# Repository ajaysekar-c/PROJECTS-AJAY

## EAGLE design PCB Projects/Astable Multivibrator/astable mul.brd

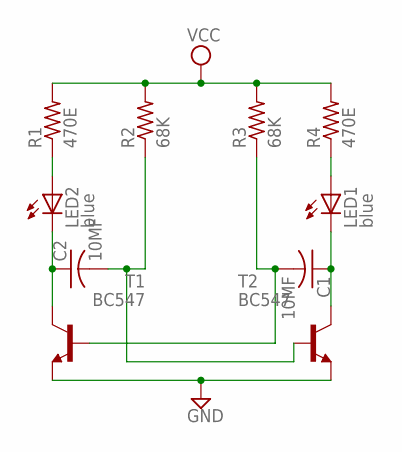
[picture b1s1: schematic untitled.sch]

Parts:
C1, C2: 10MF; C050-024X044
LED1, LED2: blue; LED5MM
R1, R4: 470E; 0207/10
R2, R3: 68K; 0207/10
T1, T2: BC547; TO92

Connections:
GND: T1.1 (E), T2.1 (E)
unnamed: LED2.A, R1.1
unnamed: C2.1, LED2.K (C), T1.3 (C)
unnamed: C1.1, LED1.K (C), T2.3 (C)
unnamed: LED1.A, R4.1
unnamed: C2.2, R2.1, T2.2 (B)
unnamed: C1.2, R3.1, T1.2 (B)
VCC: R1.2, R2.2, R3.2, R4.2

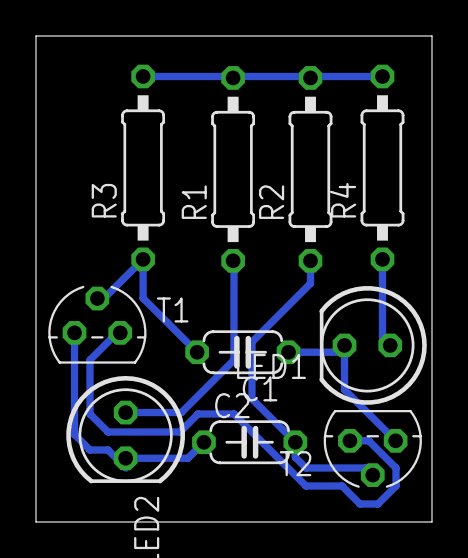
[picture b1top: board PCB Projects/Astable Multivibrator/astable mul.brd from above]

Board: 2 copper layers, 22.0 x 27.0 mm, 10 parts (0 on the bottom side), 8 nets.

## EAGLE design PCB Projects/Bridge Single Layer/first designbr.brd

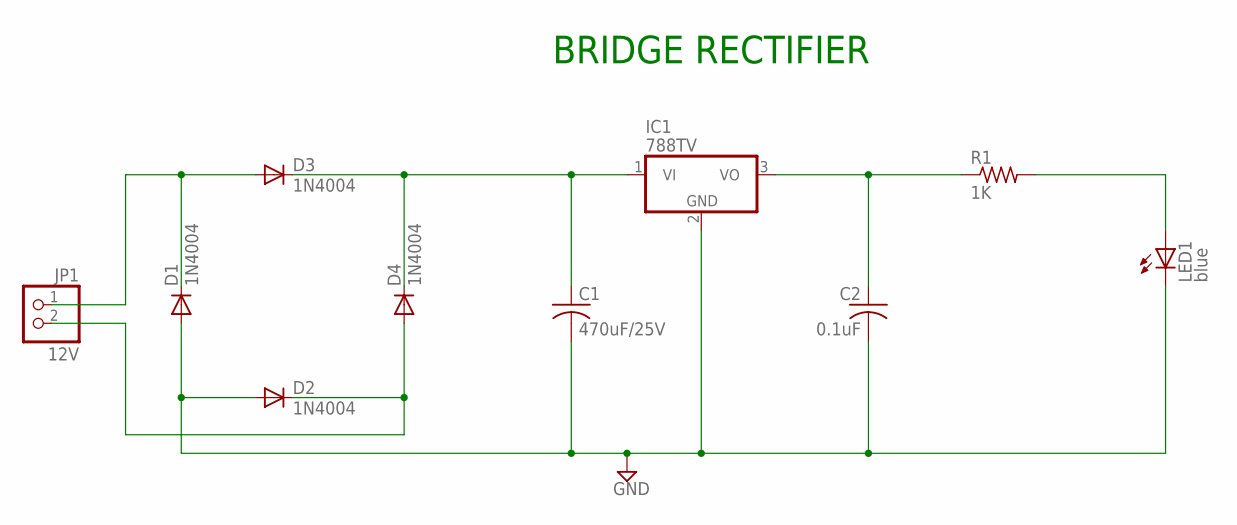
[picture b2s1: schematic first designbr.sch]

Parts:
C1: 470uF/25V; C050-025X075
C2: 0.1uF; C025-024X044
D1, D2, D3, D4: 1N4004; DO41-10
IC1: 788TV; TO220V
JP1: 12V; 1X02
LED1: blue; LED5MM
R1: 1K; 0207/10

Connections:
GND: C1.2, C2.2, D1.A, D2.A, IC1.2 (GND), LED1.K (C)
unnamed: D1.C, D3.A, JP1.1
unnamed: C1.1, D3.C, D4.C, IC1.1 (VI)
unnamed: D2.C, D4.A, JP1.2
unnamed: C2.1, IC1.3 (VO), R1.1
unnamed: LED1.A, R1.2

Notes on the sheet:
BRIDGE RECTIFIER

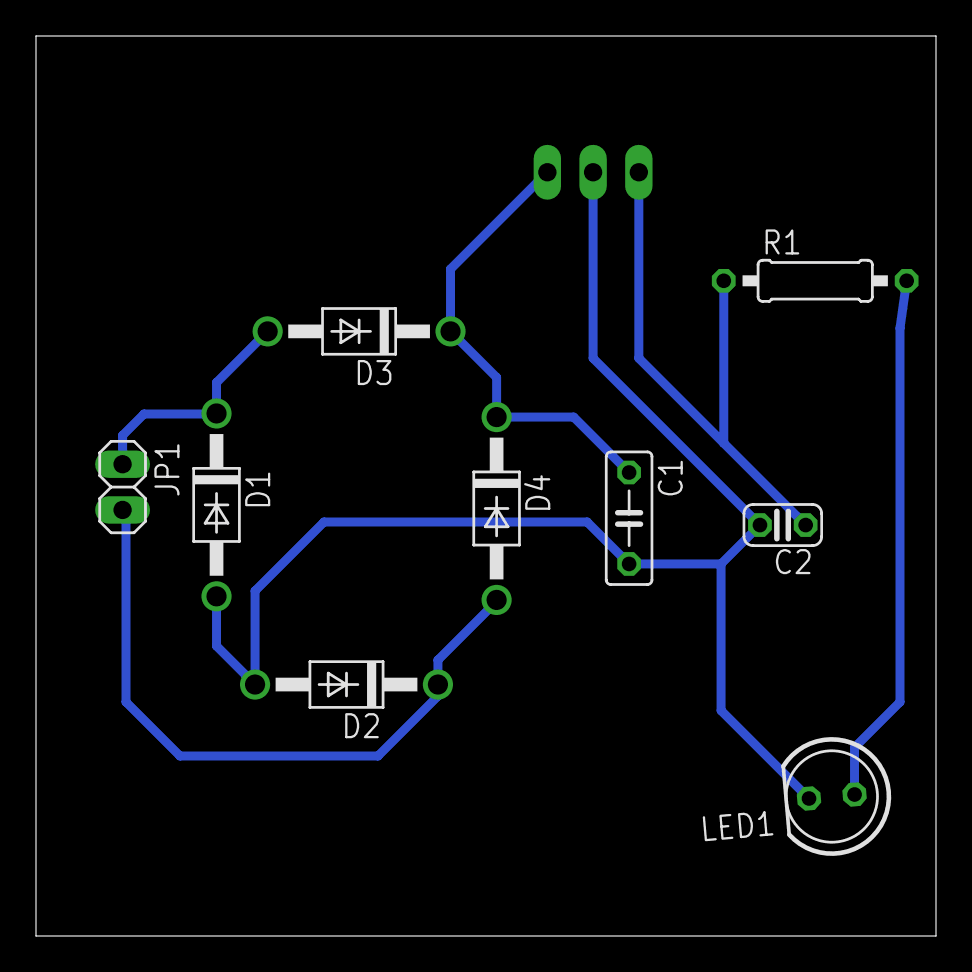
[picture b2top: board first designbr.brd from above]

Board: 2 copper layers, 50.0 x 50.0 mm, 10 parts (1 on the bottom side), 6 nets.

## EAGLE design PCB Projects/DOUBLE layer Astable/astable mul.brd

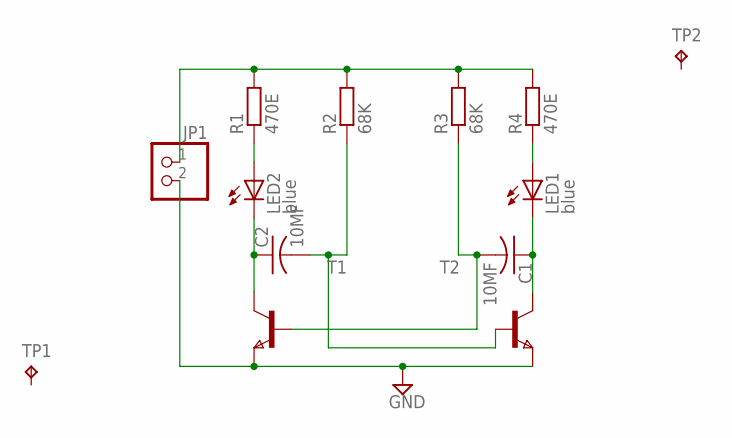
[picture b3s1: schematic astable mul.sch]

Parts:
C1, C2: 10MF; C050-025X075
JP1: PINHD-1X2; 1X02
LED1, LED2: blue; LED_1206
R1, R4: 470E; R0805
R2, R3: 68K; R0805
T1, T2: NPNSOT23; SOT-23
TP1, TP2: TPB1,27; B1,27

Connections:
GND: JP1.2, T1.2 (E), T2.2 (E)
unnamed: JP1.1, R1.2, R2.2, R3.2, R4.2
unnamed: LED2.A, R1.1
unnamed: C2.1, LED2.C, T1.1 (C)
unnamed: LED1.A, R4.1
unnamed: C1.1, LED1.C, T2.1 (C)
unnamed: C2.2, R2.1, T2.3 (B)
unnamed: C1.2, R3.1, T1.3 (B)

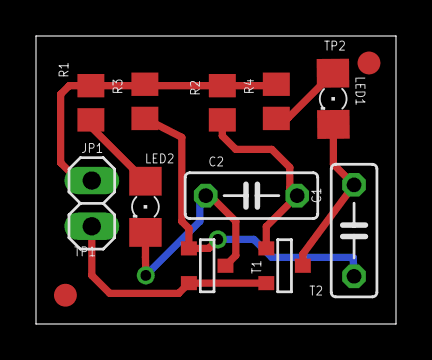
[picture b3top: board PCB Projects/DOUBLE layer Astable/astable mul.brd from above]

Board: 2 copper layers, 20.0 x 16.0 mm, 13 parts (0 on the bottom side), 8 nets.

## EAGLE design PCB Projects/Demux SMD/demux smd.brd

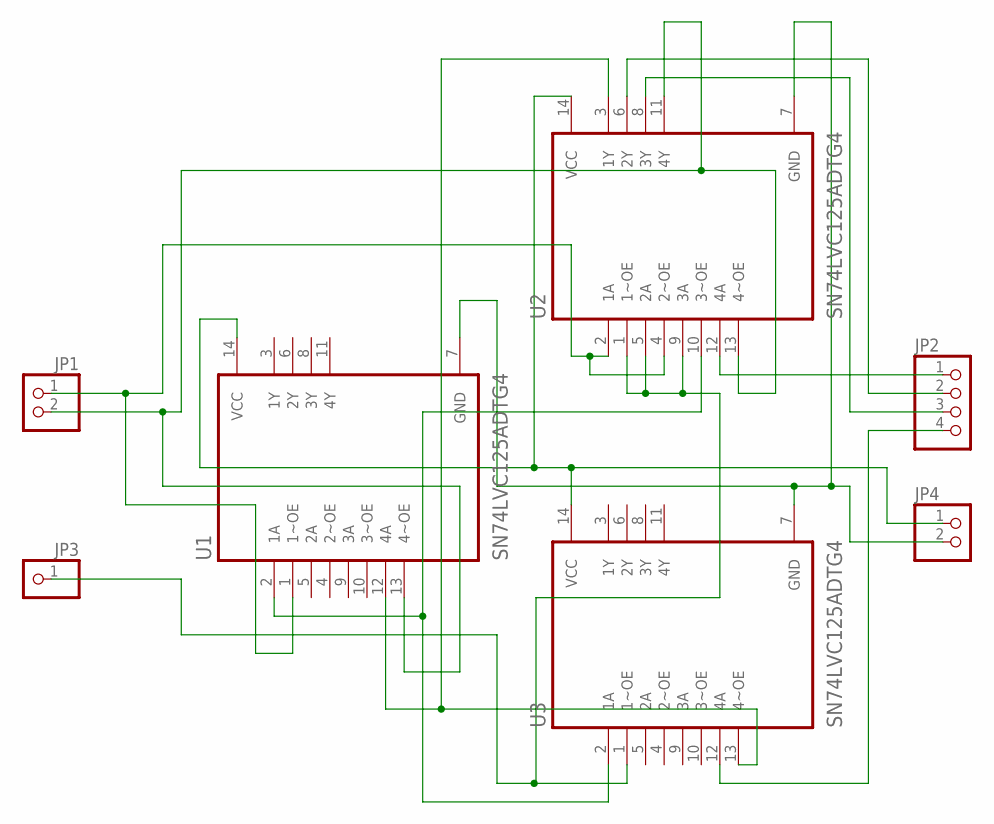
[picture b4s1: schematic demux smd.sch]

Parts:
JP1, JP4: PINHD-1X2; 1X02
JP2: PINHD-1X4; 1X04
JP3: PINHD-1X1; 1X01
U1, U2, U3: SN74LVC125ADTG4; SOIC127P600X175-14N

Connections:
unnamed: JP3.1, U2.1 (1~OE), U2.5 (2A), U2.9 (3A), U3.1 (1~OE)
unnamed: JP4.2, U1.7 (GND), U2.7 (GND), U3.7 (GND)
unnamed: JP4.1, U1.14 (VCC), U2.14 (VCC), U3.14 (VCC)
unnamed: JP2.1, U2.12 (4A)
unnamed: JP2.2, U2.6 (2Y)
unnamed: JP2.3, U2.8 (3Y)
unnamed: JP2.4, U3.12 (4A)
unnamed: U1.2 (1A), U2.10 (3~OE), U3.2 (1A)
unnamed: JP1.1, U1.1 (1~OE), U2.2 (1A), U2.4 (2~OE)
unnamed: JP1.2, U1.13 (4~OE), U2.11 (4Y), U2.13 (4~OE)
unnamed: U1.12 (4A), U2.3 (1Y), U3.13 (4~OE)

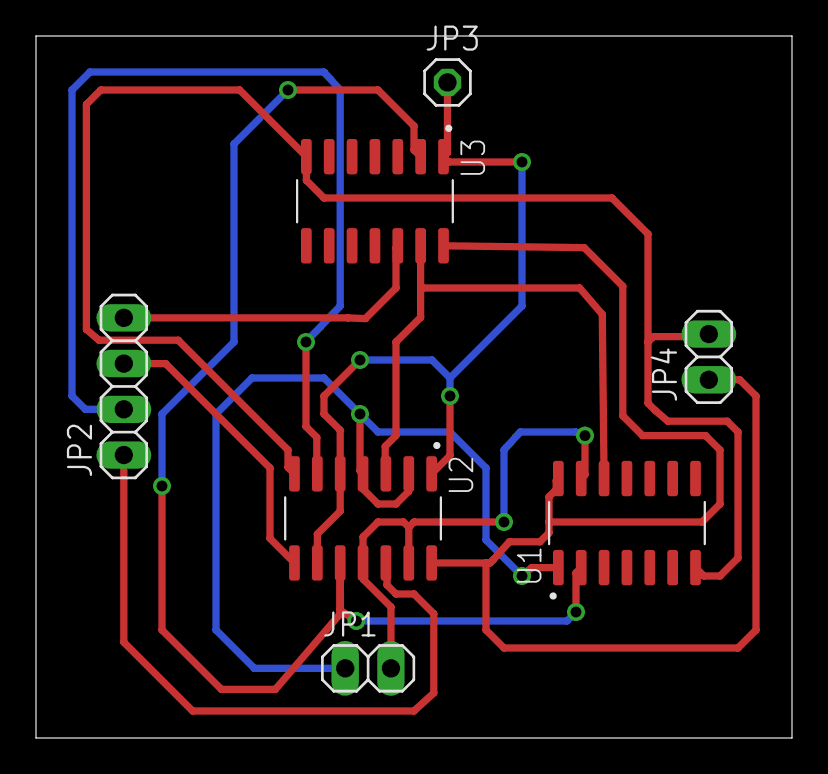
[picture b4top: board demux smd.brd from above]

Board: 2 copper layers, 42.0 x 39.0 mm, 7 parts (0 on the bottom side), 11 nets.

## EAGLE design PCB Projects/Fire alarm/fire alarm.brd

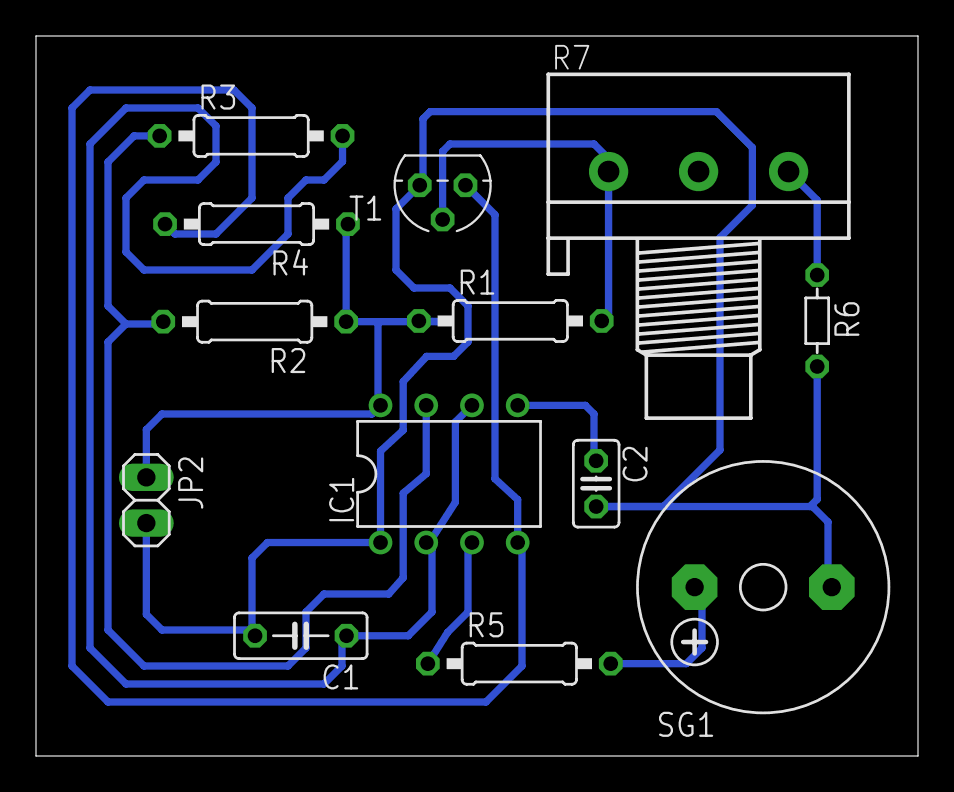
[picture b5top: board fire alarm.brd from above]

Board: 2 copper layers, 49.0 x 40.0 mm, 13 parts (0 on the bottom side), 10 nets.

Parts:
C1: 10uF; C050-025X075
C2: 0.01uF; C025-025X050
IC1: NE555N; DIL08
JP2: 1X02
R1, R3: 100k; 0207/10
R2: 1k; 0207/10
R4: 43k; 0207/10
R5: 10; 0207/10
R6: THERMISTOR-5; R-5
R7: 100k; 3RP/1610N
SG1: F/CM12P
T1: BC547; TO92

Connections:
unnamed: IC1.8, JP2.1, R1.1, R2.1, R4.1
unnamed: C1.2, C2.2, IC1.1, JP2.2, R6.2, SG1.-, T1.1
unnamed: C2.1, IC1.5
unnamed: IC1.7, R2.2, R3.1
unnamed: IC1.3, R5.1
unnamed: R5.2, SG1.+
unnamed: C1.1, IC1.2, IC1.6, R3.2
unnamed: IC1.4, R4.2, T1.3
unnamed: R1.2, R7.1, T1.2
unnamed: R6.1, R7.3
